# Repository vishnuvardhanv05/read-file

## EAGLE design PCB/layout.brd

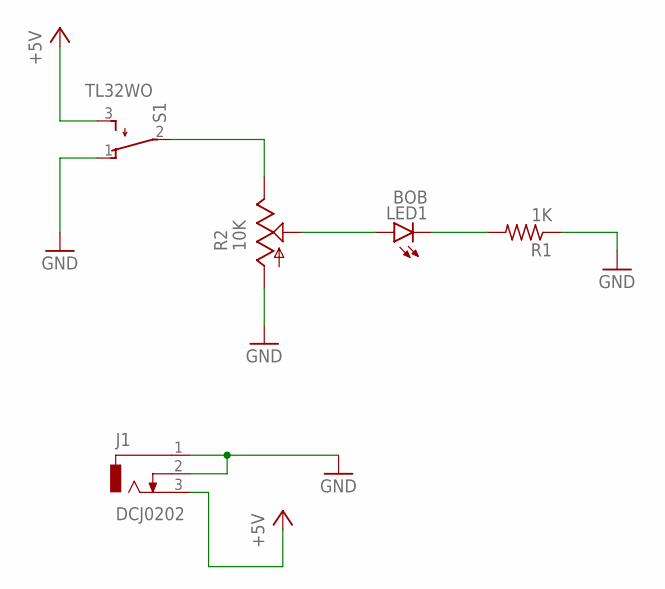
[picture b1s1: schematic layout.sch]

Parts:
J1: DCJ0202
LED1: BOB; LED5MM
R1: 1K; 0204/7
R2: 10K; RJ9W
S1: TL32WO; TL3XWO

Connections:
+5V: J1.3, S1.3 (S)
GND: J1.1, J1.2, R1.1, R2.A, S1.1 (O)
unnamed: LED1.K (C), R1.2
unnamed: R2.E, S1.2
unnamed: LED1.A, R2.S

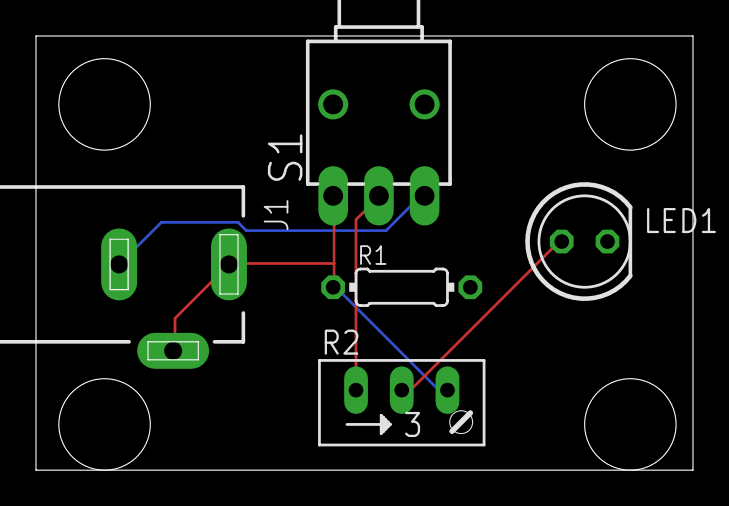
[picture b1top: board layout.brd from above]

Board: 2 copper layers, 36.5 x 24.1 mm, 6 parts (0 on the bottom side), 5 nets.

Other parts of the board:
DRILEGEND: DRILEGEND

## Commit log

2026-01-30 my pcb upload
